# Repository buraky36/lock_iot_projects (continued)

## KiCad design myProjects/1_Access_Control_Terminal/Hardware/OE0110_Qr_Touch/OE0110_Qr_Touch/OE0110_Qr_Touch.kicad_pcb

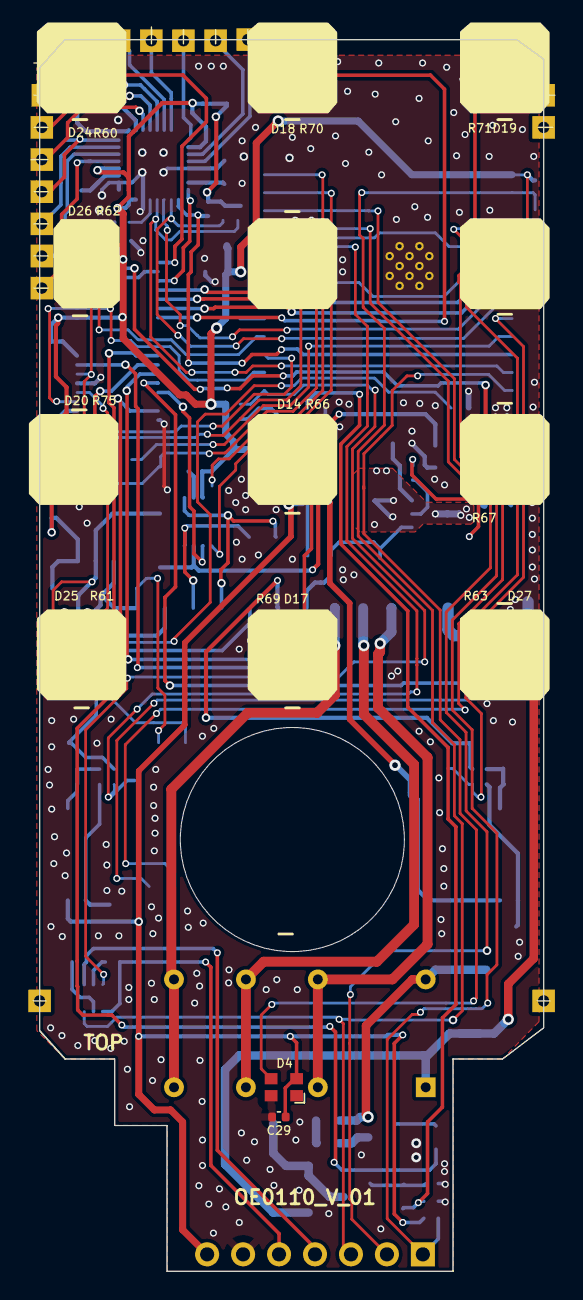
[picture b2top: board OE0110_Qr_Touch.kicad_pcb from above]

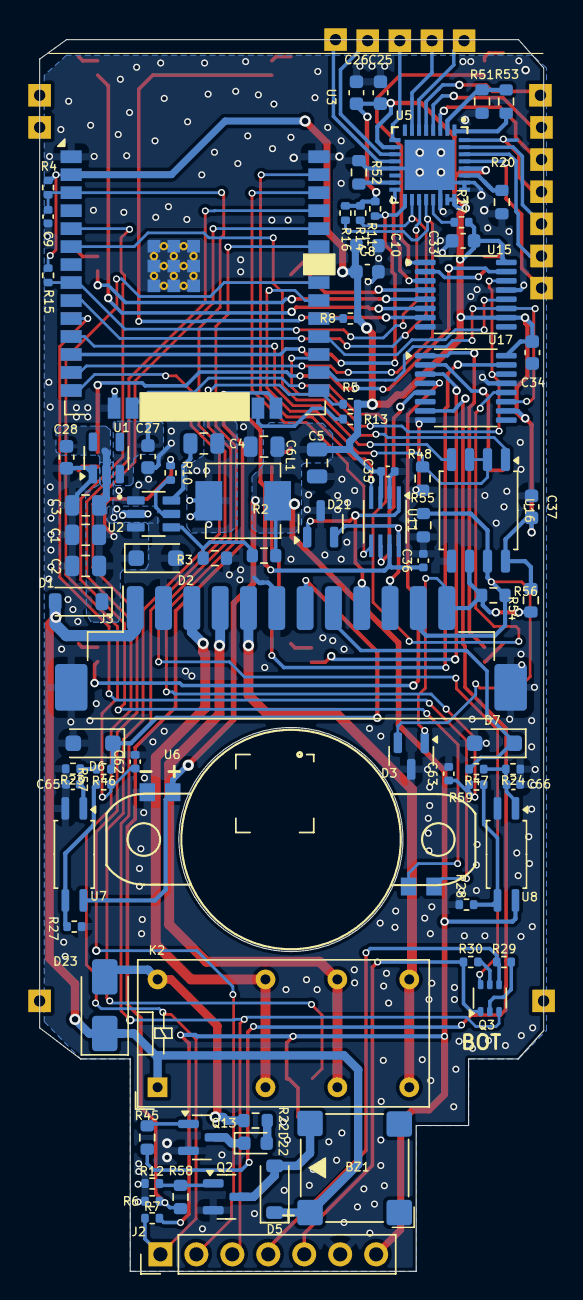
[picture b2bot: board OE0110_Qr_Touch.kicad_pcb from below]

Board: 2 copper layers, 35.6 x 87.0 mm, 128 parts (86 on the bottom side), 101 nets.

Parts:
BZ1: FUET-7525-3.6V; MagneticBuzzer_PUI_SMT-1028-T-2-R
C1, C2: 10uF/25V; C_0805_2012Metric
C3, C4: 100nF/50V; C_0805_2012Metric
C5, C6: 22uF/10V; C_0805_2012Metric
C8, C25, C27: 1uF/50V; C_0603_1608Metric
C9, C29, C35, C36: 100nF; C_0402_1005Metric
C10, C26, C28, C33, C34, C37: 100nF/50V; C_0603_1608Metric
C62, C63, C65, C66: 1nF; C_0402_1005Metric
D1, D5: 1N5819HW-7-F; D_SOD-123
D2: SMF13CA; D_SOD-123F
D3: SM712; SOT-23
D4: SK6812MINI; LED_ASMB-KTF0-0A306
D6, D7: SMF15A; D_SOD-123F
D13, D14, D15, D16, D17, D18, D19, D20, D24, D25, D26, D27: LED WHITE; LED_0603_1608Metric
D21: ESDA6V1L-GK; SOT-23
D22: Green_smd; LED_0603_1608Metric
D23: M7; D_SMA
J2: Conn_01x07; PinHeader_1x07_P2.54mm_Vertical
J3: Conn_01x12_MountingPin; Hirose_DF3EA-12P-2H_1x12-1MP_P2.00mm_Horizontal
J7, J8, J9, J10, J11, J12, J13, J14, J15, J16, J17, J18, J20, J23, J24, J25: TestPoint:TestPoint_Keystone_5015_Micro_Mini; 1x01
K2: HRS2H-S-DC12V-N; Relay_DPDT_Omron_G5V-2
L1: 3.3uH; L_Vishay_IHLP-2020
Q2, Q13: BC817; SOT-23
Q3: BC846BS; SOT-363_SC-70-6
R2: 33.2K/%1; R_0603_1608Metric
R3: 10K/%1; R_0603_1608Metric
R4, R5, R6, R7, R8, R10, R11, R12, R13, R14, R15, R16, R17, R27, R28, R29, R30: 10K; R_0402_1005Metric
R20, R51: 2M; R_0603_1608Metric
R22: 5.1K; R_0603_1608Metric
R23, R24: 510R; R_0402_1005Metric
R45: 1K; R_0603_1608Metric
R46, R47: 3.3K; R_0402_1005Metric
R48: 4.7K; R_0603_1608Metric
R52: 20K; R_0603_1608Metric
R53: 510K; R_0603_1608Metric
R54, R55, R58: 560R; R_0603_1608Metric
R56: 120R; R_0603_1608Metric
R57, R59: 100R; R_0402_1005Metric
R60, R61, R62, R63, R65, R66, R67, R68, R69, R70, R71, R75: 330R; R_0402_1005Metric
U1: TLV70450DBVR; SOT-23-5
U2: TPS562201DDCR; SOT95P280X110-6N
U3: ESP32-WROOM-32UE; ESP32-WROOM-32E
U5: TSM12M; QFN_32_5X5
U6: XR1300; XR1300_QR_READER
U7, U8: TLP185(SE; SOIC-4_4.55x2.6mm_P1.27mm
U11: TXS0102DCT; SSOP-8_2.95x2.8mm_P0.65mm
U15, U17: 74HC595PW,118; TSSOP-16_4.4x5mm_P0.65mm
U16: GM3085E; SOIC-8_5.3x5.3mm_P1.27mm

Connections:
1_LED: R60.1, U15.1 (QB)
2_LED: R70.1, U15.7 (QH)
3.3V: C5.1, C6.1, C8.1, C10.1, C25.1, C26.1, C29.2, C33.2, C34.2, C35.2, C37.2, D4.4 (VDD), J2.7, L1.2, R2.2, R4.2, R5.2, R7.2, R8.2, R11.2, R13.2, R14.2, R15.2, R16.2, R17.2, R54.1, U3.2 (VDD), U5.10 (VDD), U5.23 (P_CDEG0), U5.24 (P_CDEG1), U5.28 (VDD), U6.11 (VIN), U7.4, U8.4, U11.3 (VCCA), U15.10 (~SRCLR), U15.16 (VCC), U16.8 (VCC), U17.10 (~SRCLR), U17.16 (VCC)
3_LED: R71.1, U15.6 (QG)
5_LED: R68.1, U15.4 (QE)
6_LED: R65.1, U15.5 (QF)
7_LED: R75.1, U17.2 (QC)
8_LED: R66.1, U17.15 (QA)
9_LED: R67.1, U15.15 (QA)
10_LED: R61.1, U17.1 (QB)
11_LED: R69.1, U17.3 (QD)
12V: BZ1.4 (+), D1.2 (A), D5.1 (K), D23.1 (K), J3.1, K2.1
12_LED: R63.1, U17.4 (QE)
+5V: C27.1, C36.1, U1.3 (VOUT), U11.7 (VCCB)
/TOP/Touch_TSM12/TSM12_I2C_EN: R17.1, U5.21 (I2C_EN)
DTR: J2.5, Q3.1 (E1), R30.1
Digital_INPUT1: C62.1, R57.2, U3.31 (IO19)
ESP32_EN: C9.2, J2.3, Q3.3 (C2), R4.1, U3.3 (EN)
GND: C1.2, C2.2, C3.2, C5.2, C6.2, C8.2, C9.1, C10.2, C25.2, C26.2, C27.2, C28.2, C29.1, C33.1, C34.1, C35.1, C36.2, C37.1, C62.2, C63.2, C65.2, C66.2, D2.2 (A2), D3.3 (common), D4.2 (VSS), D6.2 (A2), D7.2 (A2), D13.1 (K), D14.1 (K), D15.1 (K), D16.1 (K), D17.1 (K), D18.1 (K), D19.1 (K), D20.1 (K), D21.3 (common), D24.1 (K), D25.1 (K), D26.1 (K), D27.1 (K), J2.6, J3.2, J3.6, J3.MP (MountPin), Q2.2 (E), Q13.2 (E), R3.1, R6.1, R12.1, R20.1, R23.1, R24.1, R27.1, R28.1, R48.2, R51.2, R52.1, R55.2, U1.1 (GND), U2.1 (GND), U3.1 (GND), U3.15 (GND), U3.38 (GND), U3.39 (GND), U5.13 (VSS), U5.22 (ID_SEL), U5.25 (P_CDEG2), U5.26 (VSS), U5.33 (VSS), U6.12 (GND), U7.2, U8.2, U11.2 (GND), U15.8 (GND), U15.13 (~OE), U16.5 (GND), U17.8 (GND), U17.13 (~OE)
GPIO0_BOOT: Q3.6 (C1), R5.1, U3.25 (IO0)
GPIO1_TXD0: J2.1, R7.1, U3.35 (TXD0/IO1)
GPIO2: R6.2, R58.2, U3.24 (IO2)
GPIO3_RXD0: J2.2, U3.34 (RXD0/IO3)
GPIO4: U3.26 (IO4), U15.11 (SRCLK), U17.11 (SRCLK)
GPIO13: U3.16 (IO13), U17.12 (RCLK)
GPIO14: R16.1, U3.13 (IO14), U5.20 (INT)
GPIO16: U3.27 (IO16), U15.14 (SER), U17.14 (SER)
GPIO17: U3.28 (IO17), U15.12 (RCLK)
GPIO18: R48.1, U3.30 (IO18), U16.2 (RE), U16.3 (DE)
GPIO21: C63.1, R59.2, U3.33 (IO21)
GPIO23: U3.37 (IO23), U11.4 (A2)
GPIO26: U3.11 (IO26), U16.4 (DI)
GPIO27: R11.1, U3.12 (IO27), U5.17 (OUT1)
GPIO32: R15.1, U3.8 (IO32), U5.19 (SDA)
GPIO33: R14.1, U3.9 (IO33), U5.18 (SCL)
GPIO34: U3.6 (IO34), U16.1 (RO)
INPUT1: D6.1 (A1), J3.7, R46.1
INPUT2: D7.1 (A1), J3.8, R47.1
unnamed: BZ1.3 (-), D5.2 (A), Q2.3 (C)
unnamed: C65.1, R23.2, R46.2, U7.1
unnamed: C66.1, R24.2, R47.2, U8.1
unnamed: C1.1, C2.1, C3.1, C28.1, D1.1 (K), D2.1 (A1), R10.1, U1.2 (VIN), U2.3 (VIN)
unnamed: D13.2 (A), R65.2
unnamed: D14.2 (A), R66.2
unnamed: D15.2 (A), R67.2
unnamed: D16.2 (A), R68.2
unnamed: D17.2 (A), R69.2
unnamed: D18.2 (A), R70.2
unnamed: D19.2 (A), R71.2
unnamed: D20.2 (A), R75.2
unnamed: D22.2 (A), R22.1
unnamed: D22.1 (K), Q13.3 (C)
unnamed: D23.2 (A), K2.16, R22.2
unnamed: D24.2 (A), R60.2
unnamed: D25.2 (A), R61.2
unnamed: D26.2 (A), R62.2
unnamed: D27.2 (A), R63.2
unnamed: J7.1, U5.29 (CS1)
unnamed: J8.1, U5.30 (CS2)
unnamed: J9.1, U5.31 (CS3)
unnamed: J10.1, U5.32 (CS4)
unnamed: J11.1, U5.3 (CS5)
unnamed: J12.1, U5.4 (CS6)
unnamed: J13.1, U5.5 (CS7)
unnamed: J14.1, U5.6 (CS8)
unnamed: J15.1, U5.7 (CS9)
unnamed: J16.1, U5.9 (CS10)
unnamed: J17.1, U5.11 (CS11)
unnamed: J20.1, U5.12 (CS12)
unnamed: Q2.1 (B), R12.2, R58.1
unnamed: Q3.2 (B1), R29.1
unnamed: Q3.5 (B2), R30.2
unnamed: Q13.1 (B), R45.2
unnamed: R27.2, R57.1, U7.3
unnamed: R28.2, R59.1, U8.3
unnamed: R10.2, U2.5 (EN)
unnamed: C4.2, L1.1, U2.2 (SW)
unnamed: C4.1, U2.6 (VBST)
unnamed: R2.1, R3.2, U2.4 (VFB)
unnamed: R52.2, U5.15 (IRBIAS)
unnamed: R53.2, U5.1 (RBIAS)
unnamed: R51.1, R53.1, U5.2 (SRBIAS)
unnamed: R20.2, U5.27 (SYNC/OPT)
QR_RX: U3.5 (SENSOR_VN), U6.9 (TXD)
QR_TX: U3.10 (IO25), U6.10 (RXD)
RELAY-1: R45.1, U17.7 (QH)
RELAY_COM: J3.3, K2.4, K2.13
RELAY_NC: J3.4, K2.6, K2.11
RELAY_NO: J3.5, K2.8, K2.9
RFID_MOSI: R8.1, U3.29 (IO5)
RFID_SCK: R13.1, U3.23 (IO15)
RGB_DIN: D4.3 (DIN), U3.14 (IO12)
RS485_A: D3.1 (A1), J3.12, R54.2, R56.1, U16.6 (A)
RS485_B: D3.2 (A2), J3.11, R55.1, R56.2, U16.7 (B)
RTS: J2.4, Q3.4 (E2), R29.2
ShiftReg1_QC: R62.1, U15.2 (QC)
TSM12_RST: U5.16 (RST), U15.3 (QD)
Wiegand-D0: D21.2 (A2), J3.10, U11.8 (B1)
Wiegand-D1: D21.1 (A1), J3.9, U11.1 (B2)
Wiegand_D0: U3.36 (IO22), U11.5 (A1)
Wiegand_OUT_EN: U11.6 (OE), U17.5 (QF)

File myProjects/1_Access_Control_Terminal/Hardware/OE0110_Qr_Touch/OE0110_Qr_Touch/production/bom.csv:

Designator,Footprint,Quantity,Value,LCSC Part #
BZ1,MagneticBuzzer_PUI_SMT-1028-T-2-R,1,FUET-7525-3.6V,
"C1, C2",0805,2,10uF/25V,
"C10, C26, C28, C33, C34, C37",0603,6,100nF/50V,
"C25, C27, C8",0603,3,1uF/50V,
"C29, C35, C36, C9",0402,4,100nF,
"C3, C4",0805,2,100nF/50V,
"C5, C6",0805,2,22uF/10V,
"C62, C63, C65, C66",0402,4,1nF,
"D1, D5",D_SOD-123,2,1N5819HW-7-F,
"D13, D14, D15, D16, D17, D18, D19, D20, D24, D25, D26, D27",0603,12,LED WHITE,
D2,D_SOD-123F,1,SMF13CA,
D21,SOT-23,1,ESDA6V1L-GK,
D22,0603,1,Green_smd,
D23,D_SMA,1,M7,
D3,SOT-23,1,SM712,
D4,LED_ASMB-KTF0-0A306,1,SK6812MINI,
"D6, D7",D_SOD-123F,2,SMF15A,
J2,PinHeader_1x07_P2.54mm_Vertical,1,Conn_01x07,
J3,Hirose_DF3EA-12P-2H_1x12-1MP_P2.00mm_Horizontal,1,Conn_01x12_MountingPin,
K2,Relay_DPDT_Omron_G5V-2,1,HRS2H-S-DC12V-N,
L1,L_Vishay_IHLP-2020,1,3.3uH,
"Q13, Q2",SOT-23,2,BC817,
Q3,SOT-363_SC-70-6,1,BC846BS,
"R10, R11, R12, R13, R14, R15, R16, R17, R27, R28, R29, R30, R4, R5, R6, R7, R8",0402,17,10K,
R2,0603,1,33.2K/%1,
"R20, R51",0603,2,2M,
R22,0603,1,5.1K,
"R23, R24",0402,2,510R,
R3,0603,1,10K/%1,
R45,0603,1,1K,
"R46, R47",0402,2,3.3K,
R48,0603,1,4.7K,
R52,0603,1,20K,
R53,0603,1,510K,
"R54, R55, R58",0603,3,560R,
R56,0603,1,120R,
"R57, R59",0402,2,100R,
"R60, R61, R62, R63, R65, R66, R67, R68, R69, R70, R71, R75",0402,12,330R,
U1,SOT-23-5,1,TLV70450DBVR,
U11,SSOP-8_2.95x2.8mm_P0.65mm,1,TXS0102DCT,
"U15, U17",TSSOP-16_4.4x5mm_P0.65mm,2,"74HC595PW,118",
U16,SOIC-8_5.3x5.3mm_P1.27mm,1,GM3085E,
U2,SOT95P280X110-6N,1,TPS562201DDCR,
U3,ESP32-WROOM-32E,1,ESP32-WROOM-32UE,
U5,QFN_32_5X5,1,TSM12M,
U6,XR1300_QR_READER,1,XR1300,
"U7, U8",SOIC-4_4.55x2.6mm_P1.27mm,2,TLP185(SE,

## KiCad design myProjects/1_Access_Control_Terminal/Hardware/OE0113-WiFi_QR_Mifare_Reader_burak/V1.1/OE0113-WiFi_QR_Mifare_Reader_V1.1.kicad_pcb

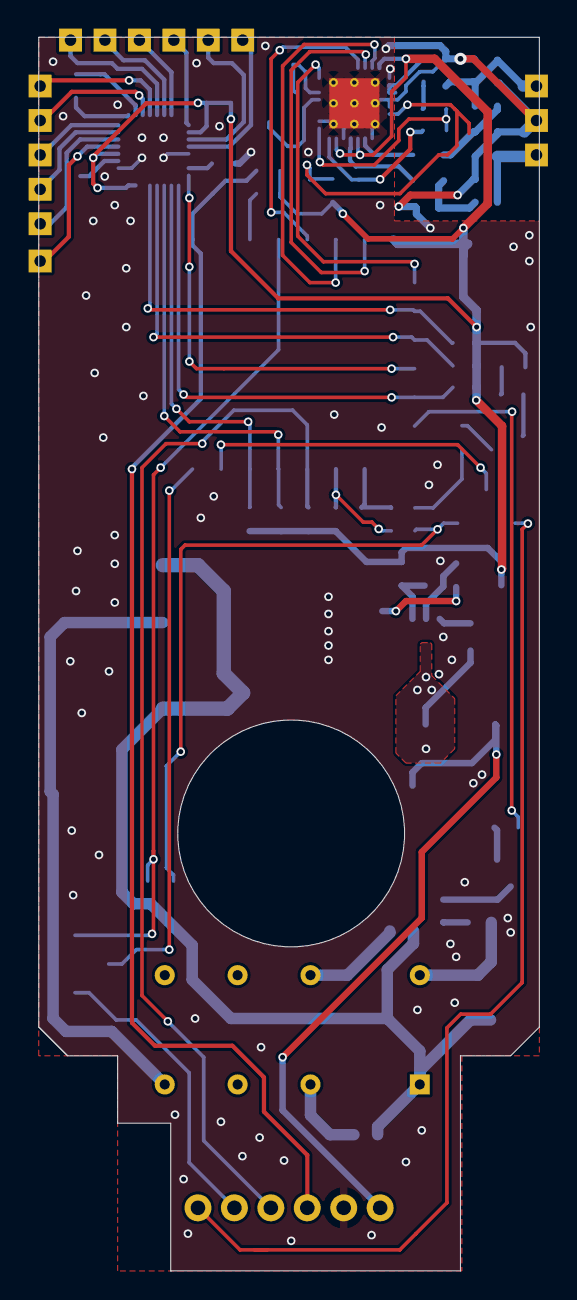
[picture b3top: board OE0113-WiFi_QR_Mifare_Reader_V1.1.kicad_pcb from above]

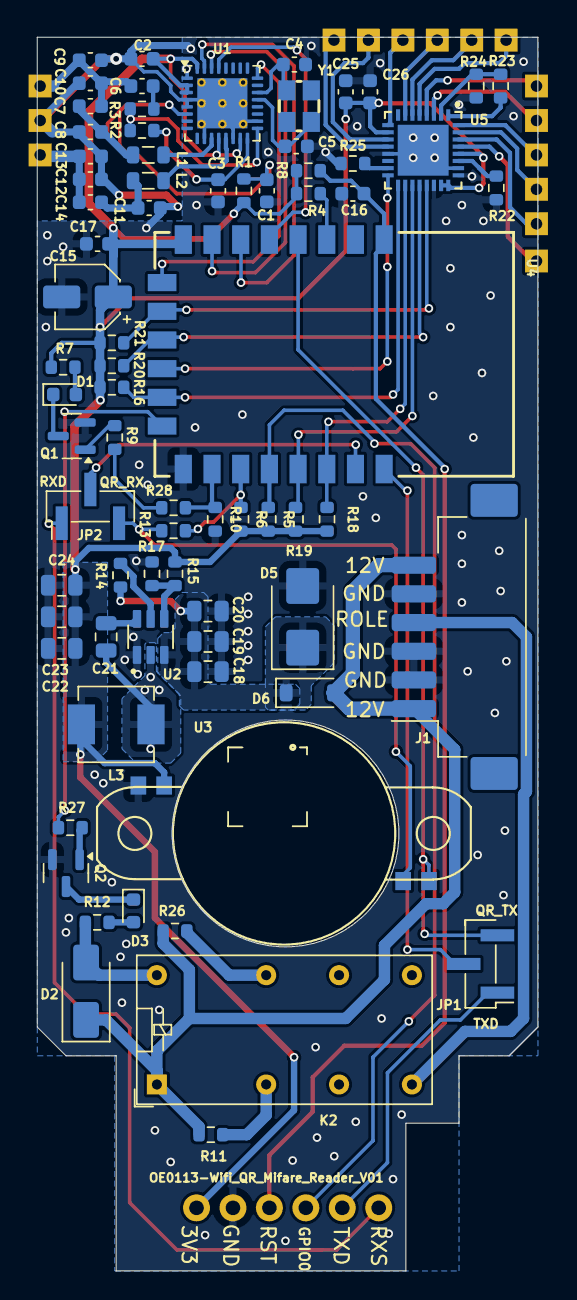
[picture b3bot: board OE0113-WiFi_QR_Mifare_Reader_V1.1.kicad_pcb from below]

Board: 2 copper layers, 34.9 x 86.0 mm, 90 parts (74 on the bottom side), 69 nets.

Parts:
C1, C17, C25: 100nF/50V; C_0603_1608Metric
C2, C3, C6: 100nF; C_0603_1608Metric
C4, C5, C7, C14: 15pF; C_0603_1608Metric
C8, C11: 47pF; C_0603_1608Metric
C9, C12: 180pF; C_0603_1608Metric
C10, C13: 10pF; C_0603_1608Metric
C15: 1uF; CP_Elec_4x5.3
C16: 1nF; C_0603_1608Metric
C18, C19: 10uF/25V; C_0805_2012Metric
C20, C21: 100nF/50V; C_0805_2012Metric
C22, C23, C24: 22uF/10V; C_0805_2012Metric
C26: 1uF/50V; C_0603_1608Metric
D1, D3: LED; LED_0603_1608Metric
D2: 1N4001; D_SMA
D5: P6SMB20A; D_SMB
D6: 1N5819HW-7-F; D_SOD-123
J1: Conn_01x06; Hirose_DF3EA-06P-2H_1x06-1MP_P2.00mm_Horizontal
J2, J3, J4, J5, J6, J7, J8, J9, J10, J11, J12, J13, J14, J15, J16: Conn_01x01; 1x01
J18: Conn_01x06; 1x06
JP1, JP2: Jumper_3_Bridged12; PinHeader_1x03_P2.00mm_Vertical_SMD_Pin1Left
K2: G5V-2; Relay_DPDT_Omron_G5V-2
L1, L2: 2.2uh; L_0805_2012Metric
L3: 3.3uH; L_Vishay_IHLP-2020
Q1, Q2: BC817; SOT-23
R1, R8, R11, R14, R17, R26: 10k; R_0603_1608Metric
R2: 820; R_0603_1608Metric
R3, R12: 5.1k; R_0603_1608Metric
R4, R5, R6, R10, R27: 12K; R_0603_1608Metric
R7: 470; R_0603_1608Metric
R9: 330; R_0603_1608Metric
R13, R28: 0R; R_0603_1608Metric
R15: 33.2K; R_0603_1608Metric
R16, R18, R19, R20, R21: 100K; R_0603_1608Metric
R22, R23: 2M; R_0603_1608Metric
R24: 510K; R_0603_1608Metric
R25: 20K; R_0603_1608Metric
U1: MFRC52201HN1,151; VQFN-32-1EP_5x5mm_P0.5mm_EP3.5x3.5mm_ThermalVias
U2: TPS562201DDCR; SOT95P280X110-6N
U3: XR1300; XR1300_QR_READER
U4: ESP-12F
U5: TSM12M; QFN_32_5X5
Y1: 27.12MHz; SMD3225-4P

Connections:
3.3V: C2.1, C15.1, C17.1, C22.1, C23.1, C24.1, C25.1, C26.1, J18.6, L3.2, R1.1, R4.2, R5.2, R6.2, R7.1, R8.1, R15.1, R16.2, R18.2, R19.2, R20.2, R21.2, U1.2 (PVDD), U1.3 (DVDD), U1.12 (TVDD), U1.15 (AVDD), U1.32 (EA), U3.11 (VIN), U4.8 (VCC), U5.10 (VDD), U5.23 (P_CDEG0), U5.24 (P_CDEG1), U5.28 (VDD)
12V: D2.1 (K), D6.2 (A), J1.1, J1.6, K2.1, R11.2, R26.2
/ANT1: C6.1, C7.1, C9.2, C10.1, J14.1
/ANT2: C12.1, C13.2, C14.1, J16.1
ESP_EN: R4.1, U4.3 (EN)
GNDD: C1.2, C2.2, C3.2, C4.2, C5.2, C8.1, C9.1, C10.2, C11.2, C12.2, C13.1, C15.2, C16.2, C17.2, C18.2, C19.2, C20.2, C22.2, C23.2, C24.2, C25.2, C26.2, D5.2 (A2), J1.2, J1.3, J1.5, J15.1, J18.5, Q1.2 (E), Q2.2 (E), R10.2, R17.2, R22.1, R23.2, R25.1, U1.1 (I2C), U1.4 (DVSS), U1.5 (PVSS), U1.10 (TVSS), U1.14 (TVSS), U1.18 (AVSS), U1.33 (EXP), U2.1 (GND), U3.12 (GND), U4.15 (GND), U5.13 (VSS), U5.22 (ID_SEL), U5.25 (P_CDEG2), U5.26 (VSS), U5.33 (VSS)
GPIO0: J18.3, R5.1, U4.18 (GPIO0)
GPIO2: R6.1, R13.1, U4.17 (GPIO2)
GPIO15: R10.1, R28.1, U4.16 (GPIO15)
unnamed: C6.2, R3.2
unnamed: C7.2, C8.2, L1.2
unnamed: C11.1, C14.2, L2.2
unnamed: D1.2 (A), R7.2
unnamed: D1.1 (K), Q1.3 (C)
unnamed: D2.2 (A), K2.16, R12.1
unnamed: D3.2 (A), R12.2
unnamed: D3.1 (K), Q2.3 (C)
unnamed: C18.1, C19.1, C20.1, D5.1 (A1), D6.1 (K), R14.1, U2.3 (VIN)
unnamed: J2.1, U5.4 (CS6)
unnamed: J3.1, U5.3 (CS5)
unnamed: J4.1, U5.32 (CS4)
unnamed: J5.1, U5.31 (CS3)
unnamed: J6.1, U5.30 (CS2)
unnamed: J7.1, U5.29 (CS1)
unnamed: J8.1, U5.5 (CS7)
unnamed: J9.1, U5.6 (CS8)
unnamed: J10.1, U5.7 (CS9)
unnamed: J11.1, U5.9 (CS10)
unnamed: J12.1, U5.11 (CS11)
unnamed: J13.1, U5.12 (CS12)
unnamed: JP1.2 (C), U4.22 (TXD)
unnamed: JP2.2 (C), U4.21 (RXD)
unnamed: K2.4, R11.1
unnamed: K2.13, R26.1
unnamed: Q1.1 (B), R9.2
unnamed: Q2.1 (B), R27.1
unnamed: C1.1, R1.2, U1.6 (NRSTPD)
unnamed: R14.2, U2.5 (EN)
unnamed: C21.2, L3.1, U2.2 (SW)
unnamed: C21.1, U2.6 (VBST)
unnamed: R15.2, R17.1, U2.4 (VFB)
unnamed: R25.2, U5.15 (IRBIAS)
unnamed: R24.1, U5.1 (RBIAS)
unnamed: R23.1, R24.2, U5.2 (SRBIAS)
unnamed: R22.2, U5.27 (SYNC/OPT)
OSC3: C5.1, U1.21 (OSCIN), Y1.1
OSC4: C4.1, U1.22 (OSCOUT), Y1.2
QR_RX: JP2.3 (B), R13.2, U3.9 (TXD)
QR_TX: JP1.3 (B), U3.10 (RXD), U4.4 (GPIO16)
RELAY1: R27.2, U4.14 (SCLK)
RFID_CS: U1.24 (SDA/NSS/RX), U4.9 (CS0)
RFID_MISO: U1.31 (D7/SCL/MISO/TX), U4.6 (GPIO12)
RFID_MOSI: U1.30 (D6/ADR_O/MOSI/MX), U4.7 (GPIO13)
RFID_SCK: U1.29 (D5/ADR_5/SCK/DTRQ), U4.5 (GPIO14)
ROLE_1: J1.4, K2.8
RST: C16.1, J18.4, R8.2, U4.1 (RST)
RX: R2.2, R3.1, U1.17 (RX)
RXD: J18.1, JP2.1 (A)
TSM12_RST: U4.12 (IO10), U5.16 (RST)
TSM_I2C_EN: R21.1, U4.10 (MISO), U5.21 (I2C_EN)
TSM_INT: R20.1, U4.11 (IO9), U5.20 (INT)
TSM_OUT1: R16.1, U4.13 (MOSI), U5.17 (OUT1)
TSM_SCL: R18.1, U4.20 (GPIO5), U5.18 (SCL)
TSM_SDA: R19.1, U4.19 (GPIO4), U5.19 (SDA)
TX11: L1.1, U1.11 (TX1)
TX12: L2.1, U1.13 (TX2)
TXD: J18.2, JP1.1 (A)
VMID: C3.1, R2.1, U1.16 (VMID)
WIFI_LED: R9.1, R28.2

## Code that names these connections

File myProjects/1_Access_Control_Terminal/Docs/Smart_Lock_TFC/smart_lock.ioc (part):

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Mcu.Name=STM32G070CBTx
Mcu.Package=LQFP48
Mcu.UserName=STM32G070CBTx
PA0.GPIOParameters=PinState,GPIO_PuPd,GPIO_Label
PA0.GPIO_Label=IC_ENABLE
PA0.GPIO_PuPd=GPIO_NOPULL
PA0.PinState=GPIO_PIN_RESET
PA0.Signal=GPIO_Output
PA1.GPIOParameters=GPIO_Label
PA1.GPIO_Label=SPI_RFID_SCK
PA1.Mode=Full_Duplex_Master
PA1.Signal=SPI1_SCK
PA10.GPIOParameters=GPIO_Label
PA10.GPIO_Label=USART_FP_Rx
PA10.Mode=Asynchronous
PA10.Signal=USART1_RX
PA11\ [PA9].GPIOParameters=GPIO_Label
PA11\ [PA9].GPIO_Label=SPI_RFID_MISO
PA11\ [PA9].Mode=Full_Duplex_Master
PA11\ [PA9].Signal=SPI1_MISO
PA12\ [PA10].GPIOParameters=GPIO_Label
PA12\ [PA10].GPIO_Label=SPI_RFID_MOSI
PA12\ [PA10].Mode=Full_Duplex_Master
PA12\ [PA10].Signal=SPI1_MOSI
PA13.Mode=Serial_Wire
PA13.Signal=SYS_SWDIO
PA14-BOOT0.Mode=Serial_Wire
PA14-BOOT0.Signal=SYS_SWCLK
PA15.GPIOParameters=GPIO_Label
PA15.GPIO_Label=LED11
PA15.Signal=GPIO_Output
PA2.GPIOParameters=GPIO_Label
PA2.GPIO_Label=WBR1_TX
PA2.Mode=Asynchronous
PA2.Signal=USART2_TX
PA3.GPIOParameters=GPIO_Label
PA3.GPIO_Label=WBR1_RX
PA3.Mode=Asynchronous
PA3.Signal=USART2_RX
PA4.GPIOParameters=GPIO_PuPd,GPIO_Label
PA4.GPIO_Label=WBR1_EN
PA4.GPIO_PuPd=GPIO_NOPULL
PA4.Signal=GPIO_Output
PA5.GPIOParameters=GPIO_Label
PA5.GPIO_Label=LED5
PA5.Signal=GPIO_Output
PA6.GPIOParameters=GPIO_Label
PA6.GPIO_Label=LED1
PA6.Signal=GPIO_Output
PA7.GPIOParameters=GPIO_Label
PA7.GPIO_Label=BAT_VOLTAGE
PA7.Mode=IN7
PA7.Signal=ADC1_IN7
PA8.GPIOParameters=GPIO_Label
PA8.GPIO_Label=FP_EN_VCC
PA8.Signal=GPIO_Output
PA9.GPIOParameters=GPIO_Label
PA9.GPIO_Label=USART_FP_Tx
PA9.Mode=Asynchronous
PA9.Signal=USART1_TX
PB0.GPIOParameters=GPIO_Label
PB0.GPIO_Label=LED4
PB0.Signal=GPIO_Output
PB1.GPIOParameters=GPIO_Label
PB1.GPIO_Label=Out_RFID_NSS
PB1.Signal=GPIO_Output
PB10.Mode=TX_Only_Simplex_Unidirect_Master
PB10.Signal=SPI2_SCK
PB11.Mode=TX_Only_Simplex_Unidirect_Master
PB11.Signal=SPI2_MOSI
PB12.GPIOParameters=GPIO_Label
PB12.GPIO_Label=Out_AP23_SBT
PB12.Signal=GPIO_Output
PB13.GPIOParameters=GPIO_Label
PB13.GPIO_Label=Motor_CCW
PB13.Signal=GPIO_Output
PB14.GPIOParameters=GPIO_Label
PB14.GPIO_Label=Motor_CW
PB14.Signal=GPIO_Output
PB15.GPIOParameters=GPIO_Label
PB15.GPIO_Label=LED6
PB15.Signal=GPIO_Output
PB2.GPIOParameters=GPIO_Label
PB2.GPIO_Label=RGB_GREEN
PB2.Signal=GPIO_Output
PB3.GPIOParameters=GPIO_Label
PB3.GPIO_Label=LED2
PB3.Signal=GPIO_Output
PB4.GPIOParameters=GPIO_Label
PB4.GPIO_Label=LED8
PB4.Signal=GPIO_Output
PB5.Signal=GPIO_Output
PB6.Signal=GPIO_Output
PB7.GPIOParameters=GPIO_Label,GPIO_ModeDefaultEXTI
PB7.GPIO_Label=TOUCH_INT
PB7.GPIO_ModeDefaultEXTI=GPIO_MODE_IT_FALLING
PB7.Signal=GPXTI7
PB8.GPIOParameters=GPIO_Label
PB8.GPIO_Label=I2C_Tsm_SCL
PB8.Mode=I2C
PB8.Signal=I2C1_SCL
PB9.GPIOParameters=GPIO_Label
PB9.GPIO_Label=I2C1_Tsm_SDA
PB9.Mode=I2C
PB9.Signal=I2C1_SDA
PC13.GPIOParameters=GPIO_Label
PC13.GPIO_Label=EXTI_FP_Touch
PC13.Signal=GPXTI13
PC14-OSC32_IN\ (PC14).GPIOParameters=GPIO_Label
PC14-OSC32_IN\ (PC14).GPIO_Label=LED7
PC14-OSC32_IN\ (PC14).Signal=GPIO_Output
PC15-OSC32_OUT\ (PC15).GPIOParameters=GPIO_Label
PC15-OSC32_OUT\ (PC15).GPIO_Label=LED10
PC15-OSC32_OUT\ (PC15).Signal=GPIO_Output
PC6.GPIOParameters=GPIO_Label
PC6.GPIO_Label=LED9
PC6.Signal=GPIO_Output
PC7.GPIOParameters=GPIO_Label
PC7.GPIO_Label=LED12
PC7.Signal=GPIO_Output
PD0.GPIOParameters=GPIO_Speed,GPIO_PuPd,GPIO_Label
PD0.GPIO_Label=TSM_RESET
PD0.GPIO_PuPd=GPIO_PULLDOWN
PD0.GPIO_Speed=GPIO_SPEED_FREQ_HIGH
PD0.Signal=GPIO_Output
PD1.GPIOParameters=GPIO_Label
PD1.GPIO_Label=LED3
PD1.Signal=GPIO_Output
PD2.GPIOParameters=GPIO_Label
PD2.GPIO_Label=RGB_BLUE
PD2.Signal=GPIO_Output
PD3.GPIOParameters=GPIO_Label
PD3.GPIO_Label=RGB_RED
PD3.Signal=GPIO_Output
PF0-OSC_IN\ (PF0).GPIOParameters=GPIO_PuPd,GPIO_Label
PF0-OSC_IN\ (PF0).GPIO_Label=MOTOR_ENABLE
PF0-OSC_IN\ (PF0).GPIO_PuPd=GPIO_NOPULL
PF0-OSC_IN\ (PF0).Signal=GPIO_Output
PF1-OSC_OUT\ (PF1).GPIOParameters=GPIO_Label,GPIO_ModeDefaultEXTI
PF1-OSC_OUT\ (PF1).GPIO_Label=SYSTEM_RESET_INT
PF1-OSC_OUT\ (PF1).GPIO_ModeDefaultEXTI=GPIO_MODE_IT_RISING
PF1-OSC_OUT\ (PF1).Signal=GPXTI1
RCC.HSE_VALUE=8000000
RCC.SYSCLKFreq_VALUE=64000000
RCC.SYSCLKSource=RCC_SYSCLKSOURCE_PLLCLK
board=custom

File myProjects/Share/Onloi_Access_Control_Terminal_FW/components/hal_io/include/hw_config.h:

#ifndef HW_CONFIG_H
#define HW_CONFIG_H

#include <stdint.h>

// Hardware Versions (Compile / internal index)
#define HW_VERSION_PIN_QR     1  // OE0113
#define HW_VERSION_PIN_RFID   2  // OE0111
#define HW_VERSION_RFID_ONLY  3  // OE0112

// Hardware Product Codes
#define PRODUCT_ID_PIN_QR     0x0113
#define PRODUCT_ID_PIN_RFID   0x0111
#define PRODUCT_ID_RFID_ONLY  0x0112

// Capability flags derived from compilation version
#if COMPILE_HW_VERSION == HW_VERSION_PIN_QR
    #define HW_HAS_KEYPAD         1
    #define HW_HAS_QR             1
    #define HW_HAS_RFID           0
    #define HW_HAS_MASTER_CODE    1
    #define HW_BOOT_MASTER_ENROLL 0
#elif COMPILE_HW_VERSION == HW_VERSION_PIN_RFID
    #define HW_HAS_KEYPAD         1
    #define HW_HAS_QR             0
    #define HW_HAS_RFID           1
    #define HW_HAS_MASTER_CODE    1
    #define HW_BOOT_MASTER_ENROLL 0
#elif COMPILE_HW_VERSION == HW_VERSION_RFID_ONLY
    #define HW_HAS_KEYPAD         0
    #define HW_HAS_QR             0
    #define HW_HAS_RFID           1
    #define HW_HAS_MASTER_CODE    0
    #define HW_BOOT_MASTER_ENROLL 1
#endif

extern char device_code_str[32];
extern char ble_name_str[64];

// The active hardware version is determined dynamically at boot
extern uint8_t active_hw_version;

// Firmware / Hardware information getters
uint16_t app_get_product_id(void);
uint8_t app_get_hardware_revision(void);
uint32_t app_get_firmware_version(void);

// PIN DEFINITIONS

// RFID (MFRC522)
#define PIN_RFID_MOSI   5
#define PIN_RFID_MISO   36
#define PIN_RFID_SCK    15
#define PIN_RFID_CS     0
#define PIN_RFID_IRQ    35

// QR Scanner (XR1300)
#define PIN_QR_TX       25
#define PIN_QR_RX       39

// RS485
#define PIN_RS485_RX    34
#define PIN_RS485_TX    26
#define PIN_RS485_DE    18

// Touch Keypad (TSM12)
#define PIN_TSM_SDA     32
#define PIN_TSM_SCL     33
#define PIN_TSM_I2C_EN  27
#define PIN_TSM_INT     14

// Shift Registers (74HC595 U1 & U2)
#define PIN_SHIFT_LATCH1 17
#define PIN_SHIFT_LATCH2 13
#define PIN_SHIFT_DATA   16
#define PIN_SHIFT_CLK    4

// Wiegand
#define PIN_WIEGAND_D0   22
#define PIN_WIEGAND_D1   23

// Peripherals
#define PIN_WS2812B_RGB  12
#define PIN_BUZZER_PWM   2

// Digital Inputs
#define PIN_DIGITAL_IN1  19
#define PIN_DIGITAL_IN2  21

#endif // HW_CONFIG_H

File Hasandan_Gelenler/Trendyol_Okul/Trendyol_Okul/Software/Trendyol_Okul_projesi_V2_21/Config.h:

#ifndef CONFIG_H
#define CONFIG_H

#include <Arduino.h>

// =============================================================
// PIN DEFINITIONS
// =============================================================
#define I2C_SDA_PIN 4 // D2 (GPIO4)
#define I2C_SCL_PIN 5 // D1 (GPIO5)

#define RELAY_PIN  15  //  (GPIO15)
#define BUZZER_PIN 14 // D5 (GPIO14)

#define QR_RX_PIN 13 // D7 (GPIO13)
#define QR_TX_PIN 12 // D6 (GPIO12)

// =============================================================
// DEFAULTS
// =============================================================
#define DEFAULT_AP_SSID_PREFIX "Login_"
#define DEFAULT_AP_PASSWORD "Barfas2015"
#define DEFAULT_WEB_USERNAME "admin"
#define DEFAULT_WEB_PASSWORD "admin123"

#define AP_CHANNEL 1
#define AP_HIDDEN false
#define AP_MAX_CONN 4

// =============================================================
// SYSTEM CONSTANTS
// =============================================================
#define FIRMWARE_VERSION "2.2.1"
#define CONFIG_FILE_PATH "/config.json"

// =============================================================
// SECURITY CONSTANTS
// =============================================================
static const uint8_t AES_KEY[32] = {'X', '/', 'F', 'J', 'l', 'K', 'H', 'J',
                                    'u', 'c', 'O', 'p', '4', 'j', '1', 'P',
                                    'h', 'A', '2', 'r', 'P', '6', 'q', 'o',
                                    '7', 'P', '8', 'N', 'k', 'J', 'E', 'E'};

// =============================================================
// DATA STRUCTURES
// =============================================================
struct DeviceConfig {
  char deviceId[32];
  char updateDate[20];
  char wifiSsid[32];     // Custom SSID
  char wifiPassword[32]; // Custom WiFi Pass
  char webUsername[32];  // Custom Web User
  char webPassword[32];  // Custom Web Pass

  DeviceConfig() {
    // Defaults are applied in ConfigManager if file doesn't exist
    // or here for safety
    strcpy(deviceId, "00000");
    strcpy(updateDate, "2026-01-01 00:00:00");

    // Generate Default SSID with ChipID
    char defaultSsid[32];
    snprintf(defaultSsid, sizeof(defaultSsid), "%s%06X", DEFAULT_AP_SSID_PREFIX,
             ESP.getChipId());

    strcpy(wifiSsid, defaultSsid);
    strcpy(wifiPassword, DEFAULT_AP_PASSWORD);
    strcpy(webUsername, DEFAULT_WEB_USERNAME);
    strcpy(webPassword, DEFAULT_WEB_PASSWORD);
  }
};

#endif
